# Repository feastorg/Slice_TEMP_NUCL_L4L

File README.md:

# Slice Template

Template for creating BREAD slices. Features STM32 Nucleo32, large dimensions (100x145mm), 4 layers.

## Introduction

[Short introduction on the project.]

## Usage

[Explain how to use the project. Include examples and screenshots if applicable.]

## Documentation

Please refer to the [docs](/docs) for more info.

---

<div align="center">
  
</div>

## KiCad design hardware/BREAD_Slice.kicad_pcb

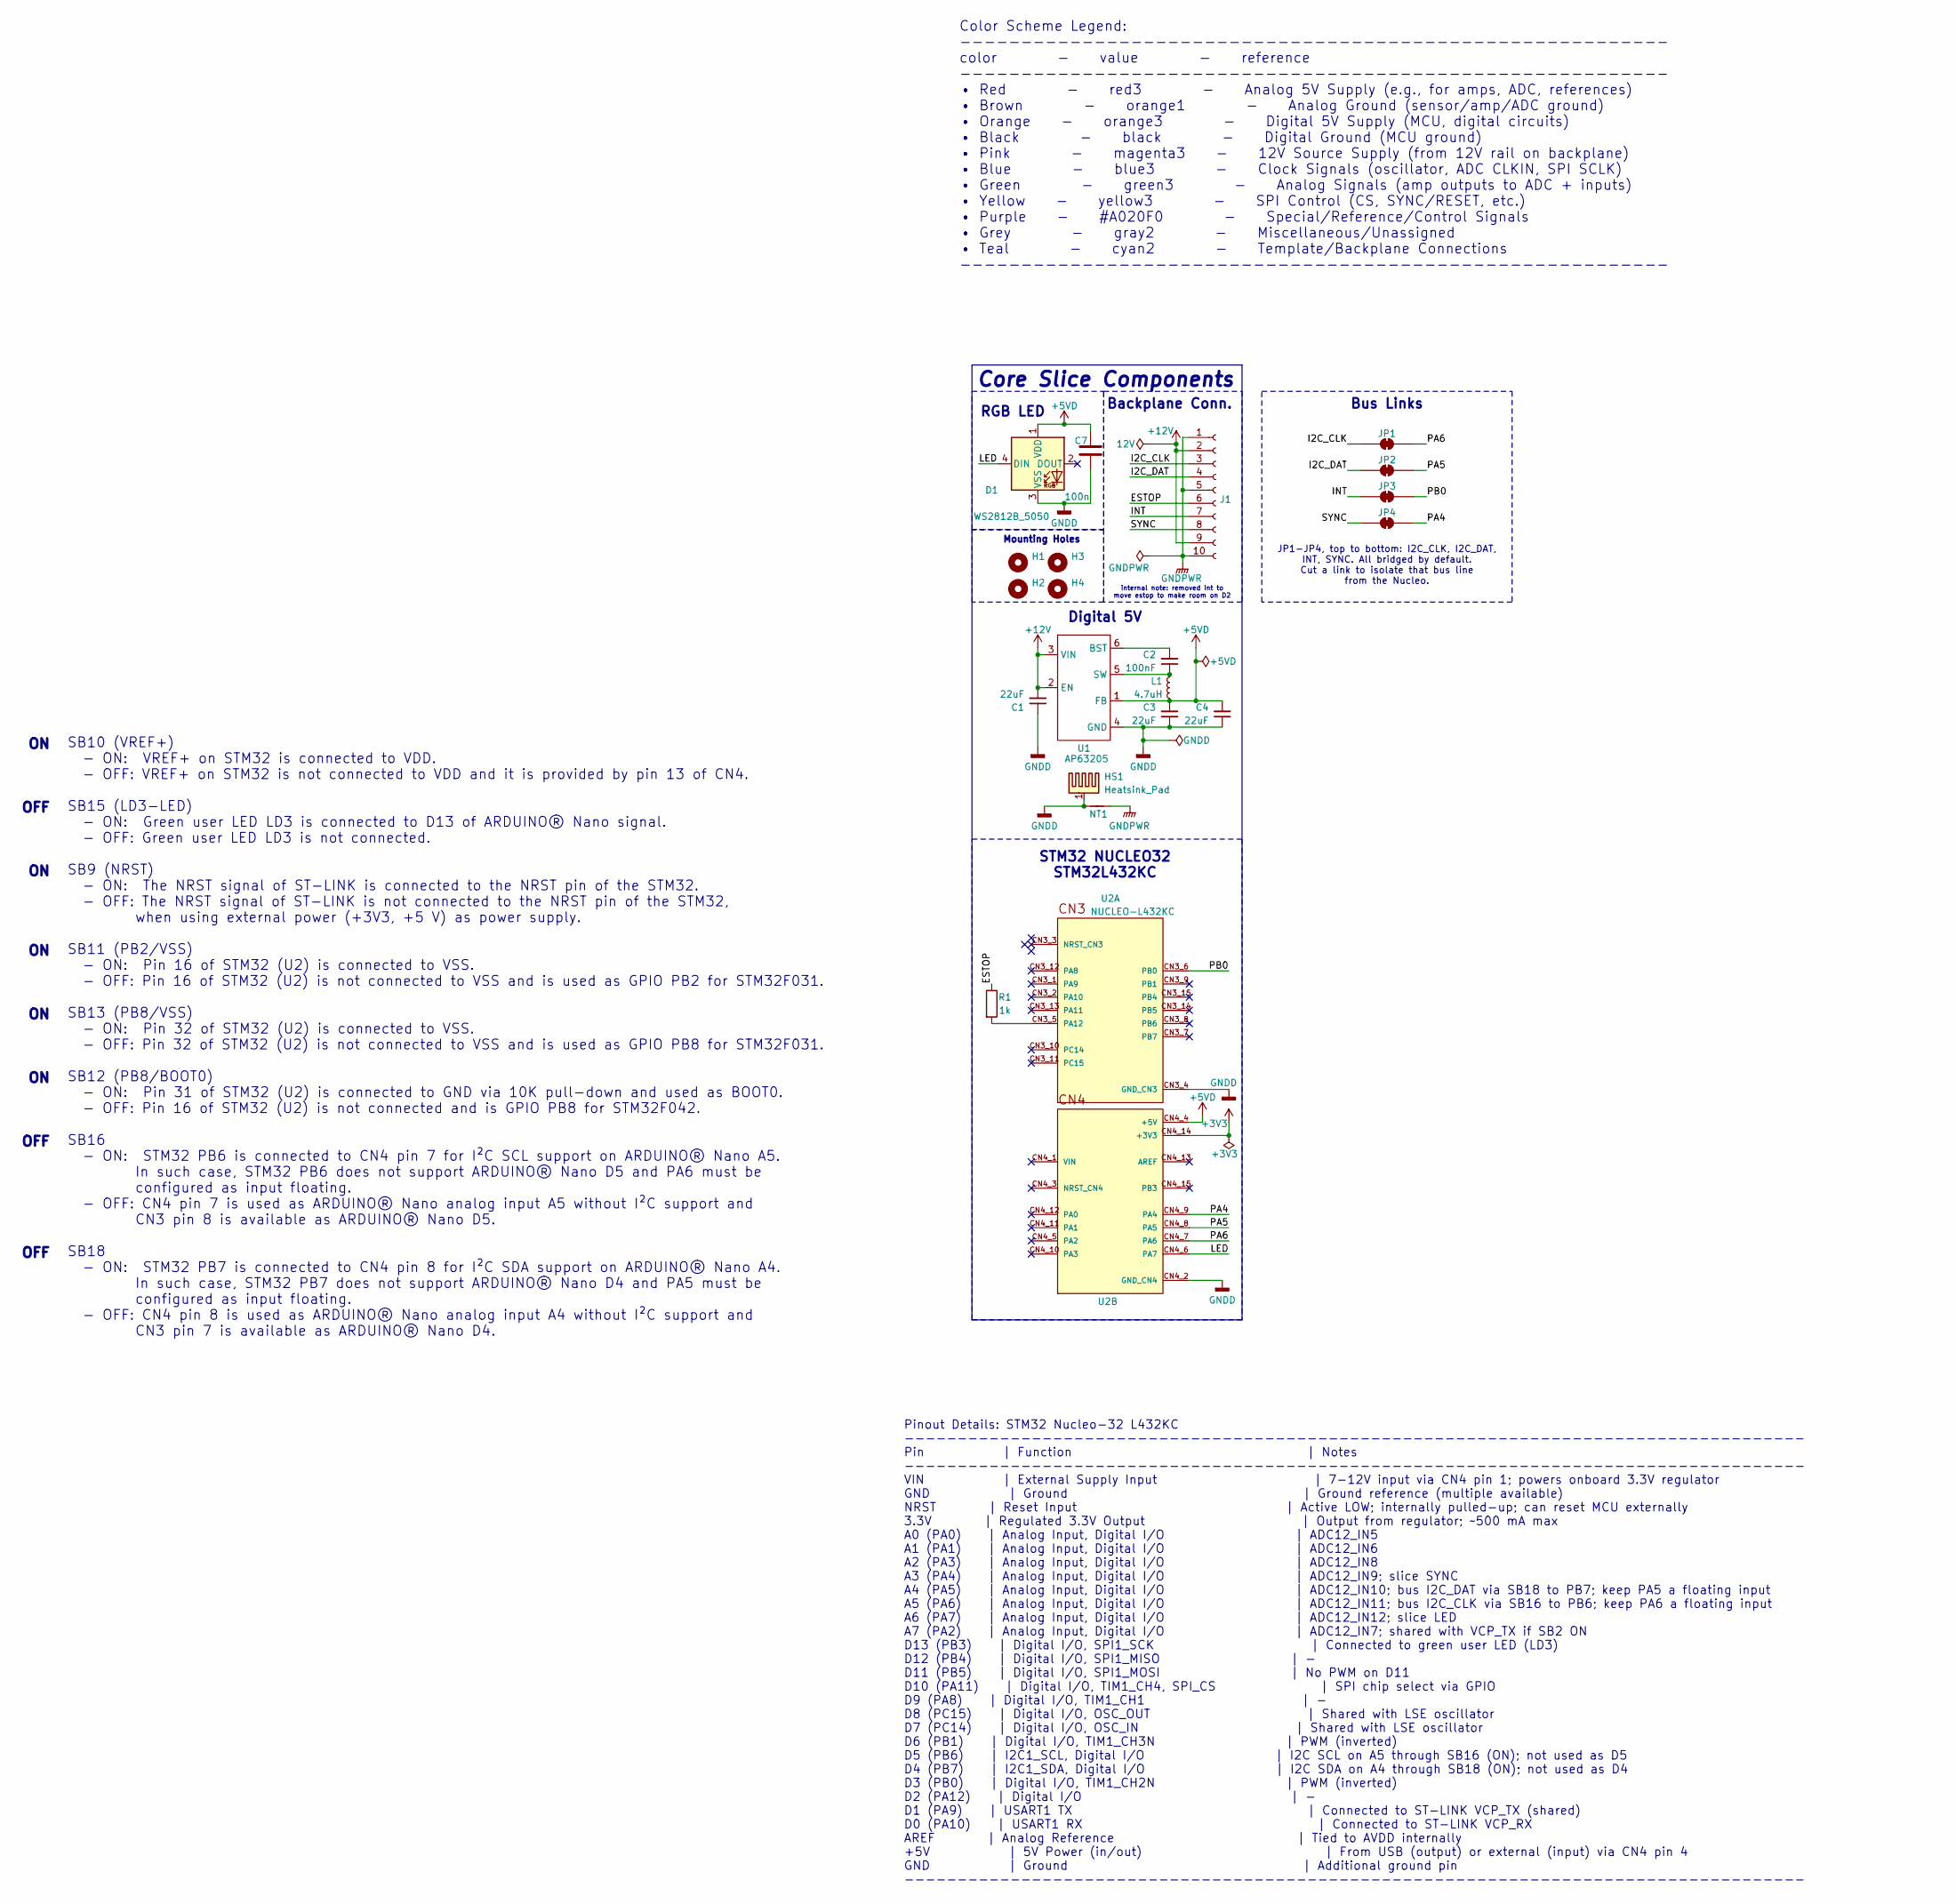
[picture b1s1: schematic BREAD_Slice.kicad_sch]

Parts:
C1, C3, C4: 22uF; C_1206_3216Metric
C2: 100nF; C_1206_3216Metric
C7: 100n; C_0603_1608Metric_Pad1.08x0.95mm_HandSolder
D1: WS2812B_5050; WS2812-5050-4PIN
H1, H2, H3, H4: MountingHole; MountingHole_5mm
HS1: Heatsink_Pad; Thermal_Pad
J1: Conn_01x10_Female; PinSocket_1x10_P2.54mm_Horizontal
JP1: I2C_CLK bus link; SolderJumper-2_P1.3mm_Bridged_RoundedPad1.0x1.5mm
JP2: I2C_DAT bus link; SolderJumper-2_P1.3mm_Bridged_RoundedPad1.0x1.5mm
JP3: INT bus link; SolderJumper-2_P1.3mm_Bridged_RoundedPad1.0x1.5mm
JP4: SYNC bus link; SolderJumper-2_P1.3mm_Bridged_RoundedPad1.0x1.5mm
L1: 4.7uH; L_1210_3225Metric
NT1: NetTie_2; NetTie-2_SMD_Pad2.0mm
R1: 1k; R_0603_1608Metric_Pad0.98x0.95mm_HandSolder
U1: AP63205; TSOT-23-6
U2: NUCLEO-L432KC; MODULE_NUCLEO-L432KC; PARTREV N/A

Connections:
+3V3: U2.CN4_14 (+3V3)
+5VD: C3.2, C4.2, C7.1, D1.1 (VDD), L1.2, U1.1 (FB), U2.CN4_4 (+5V)
+12V: C1.2, J1.2, J1.9, U1.2 (EN), U1.3 (VIN)
/ESTOP: J1.6, R1.1
/I2C_CLK: J1.3, JP1.1 (A)
/I2C_DAT: J1.4, JP2.1 (A)
/INT: J1.7, JP3.1 (A)
/LED: D1.4 (DIN), U2.CN4_6 (PA7)
/PA4: JP4.2 (B), U2.CN4_9 (PA4)
/PA5: JP2.2 (B), U2.CN4_8 (PA5)
/PA6: JP1.2 (B), U2.CN4_7 (PA6)
/PB0: JP3.2 (B), U2.CN3_6 (PB0)
/SYNC: J1.8, JP4.1 (A)
GNDD: C1.1, C3.1, C4.1, C7.2, D1.3 (VSS), HS1.1, NT1.1, U1.4 (GND), U2.CN3_4 (GND_CN3), U2.CN4_2 (GND_CN4)
GNDPWR: J1.1, J1.5, J1.10, NT1.2
unnamed: C2.2, U1.6 (BST)
unnamed: C2.1, L1.1, U1.5 (SW)
unnamed: R1.2, U2.CN3_5 (PA12)

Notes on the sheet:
Bus Links
JP1-JP4, top to bottom: I2C_CLK, I2C_DAT, INT, SYNC. All bridged by default. Cut a link to isolate that bus line from the Nucleo.
ON OFF ON ON ON ON OFF OFF
internal note: removed int to move estop to make room on D2
Backplane Conn.
Color Scheme Legend: ---------------------------------------------------------- color - value - reference ---------------------------------------------------------- • Red - red3 - Analog 5V Supply (e.g., for amps, ADC, references) • Brown - orange1 - Analog Ground (sensor/amp/ADC ground) • Orange -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
Core Slice Components
SB10 (VREF+) - ON: VREF+ on STM32 is connected to VDD. - OFF: VREF+ on STM32 is not connected to VDD and it is provided by pin 13 of CN4. SB15 (LD3-LED) - ON: Green user LED LD3 is connected to D13 of ARDUINO® Nano signal. - OFF: Green user LED LD3 is not connected. SB9 (NRST) - ON: The NRST signal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
Digital 5V
STM32 NUCLEO32 STM32L432KC
Pinout Details: STM32 Nucleo-32 L432KC ------------------------------------------------------------------------------------- Pin | Function | Notes ------------------------------------------------------------------------------------- VIN | External Supply Input | 7-12V input via CN4 pin 1; powers o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
RGB LED
Mounting Holes

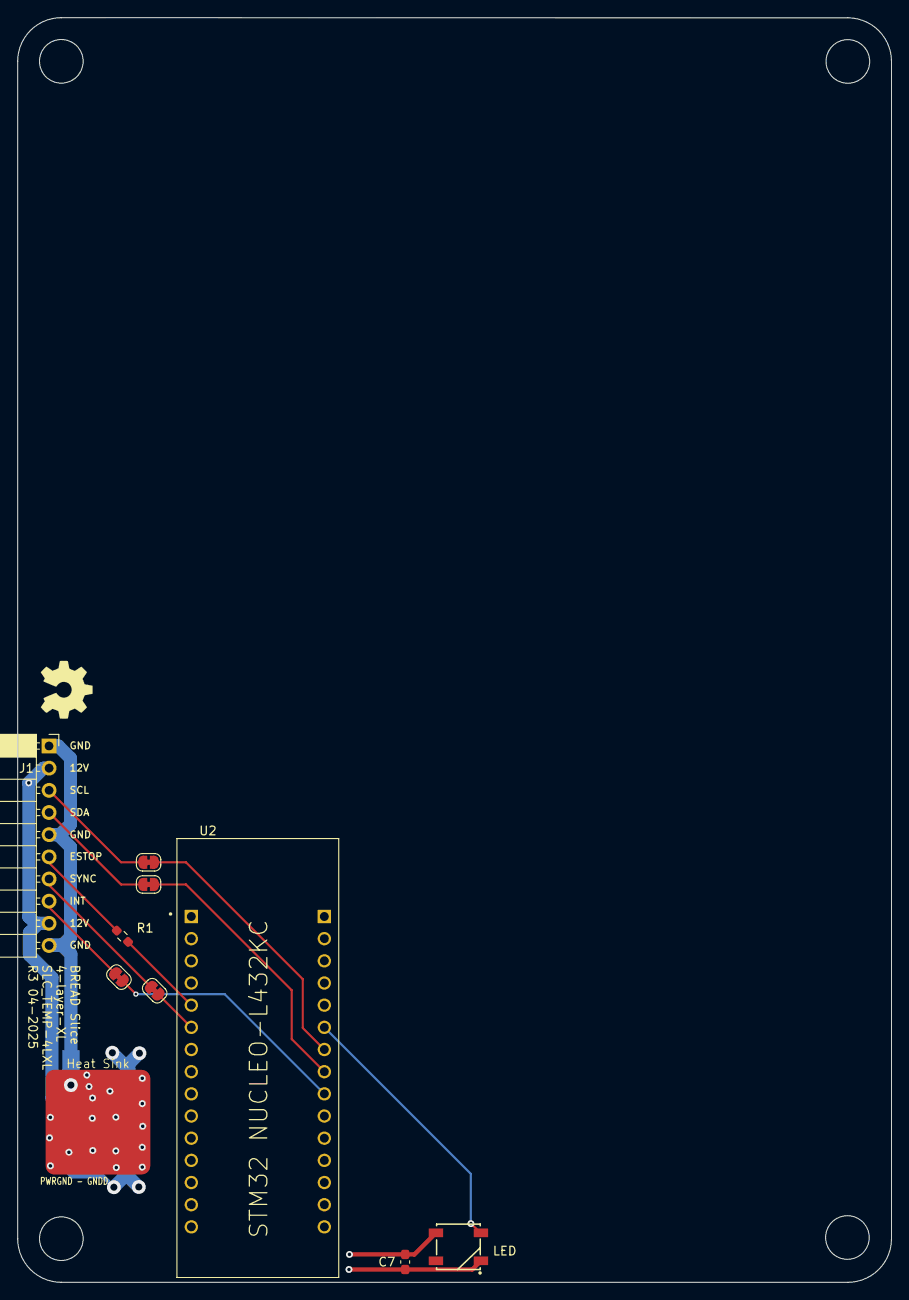
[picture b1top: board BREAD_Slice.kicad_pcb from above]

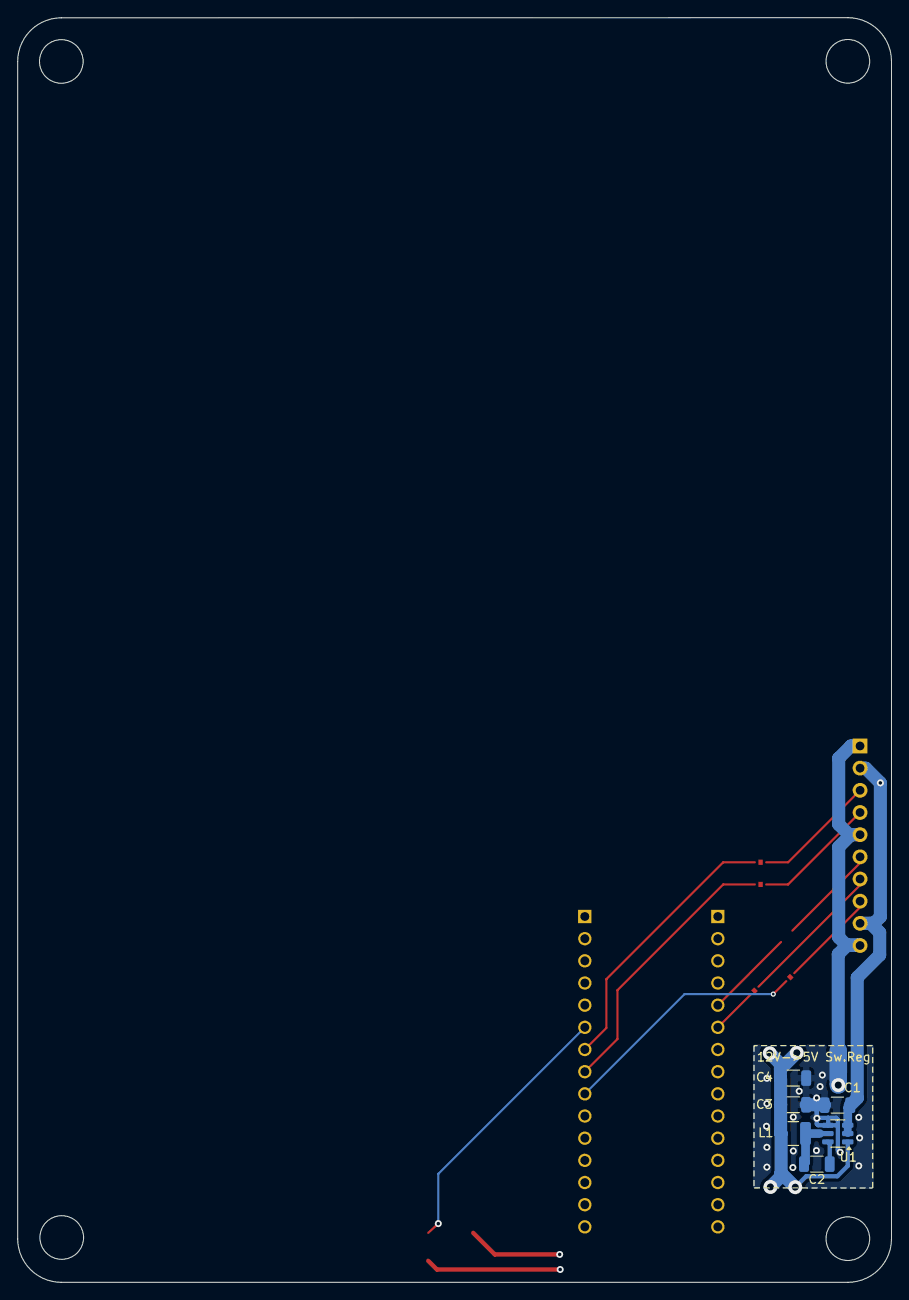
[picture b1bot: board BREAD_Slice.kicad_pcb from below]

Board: 4 copper layers, 100.1 x 144.9 mm, 22 parts (7 on the bottom side), 17 nets.

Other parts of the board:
Logo1: Logo_Open_Hardware_Small; OSHW-Symbol_6.7x6mm_SilkScreen
